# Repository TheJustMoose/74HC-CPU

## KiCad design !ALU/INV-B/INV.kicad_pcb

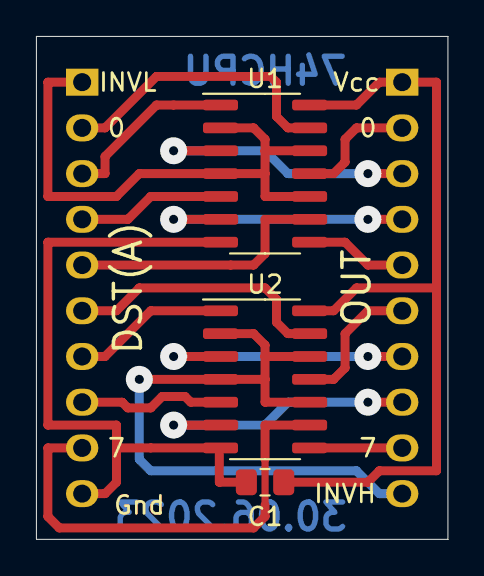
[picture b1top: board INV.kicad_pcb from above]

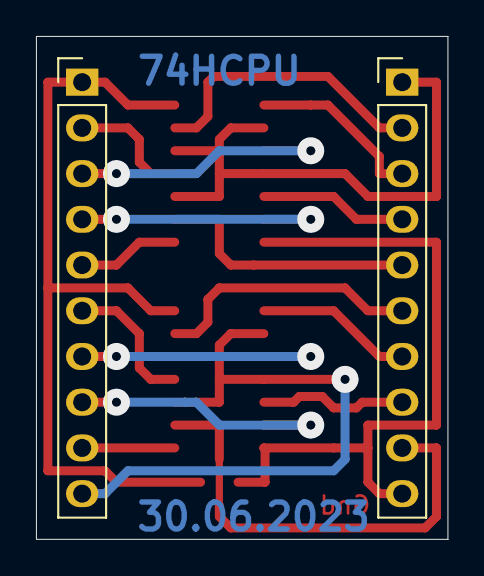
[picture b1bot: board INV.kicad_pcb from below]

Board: 2 copper layers, 22.9 x 27.9 mm, 5 parts (2 on the bottom side), 20 nets.

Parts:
C1: 0.1uF; C_0805_2012Metric_Pad1.18x1.45mm_HandSolder
J1, J2: Conn_01x10_Male; PinHeader_1x10_P2.54mm_Vertical
U1, U2: 74HC86; SO-14_3.9x8.65mm_P1.27mm

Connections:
/D0: J1.2, U1.13
/D1: J1.3, U1.1
/D2: J1.4, U1.5
/D3: J1.5, U1.9
/D4: J1.6, U2.13
/D5: J1.7, U2.1
/D6: J1.8, U2.5
/D7: J1.9, U2.9
/INVH: J2.10, U2.2, U2.4, U2.10, U2.12
/INVL: J1.1, U1.2, U1.4, U1.10, U1.12
/O0: J2.2, U1.11
/O1: J2.3, U1.3
/O2: J2.4, U1.6
/O3: J2.5, U1.8
/O4: J2.6, U2.11
/O5: J2.7, U2.3
/O6: J2.8, U2.6
/O7: J2.9, U2.8
GND: C1.2, J1.10, U1.7, U2.7
VCC: C1.1, J2.1, U1.14, U2.14

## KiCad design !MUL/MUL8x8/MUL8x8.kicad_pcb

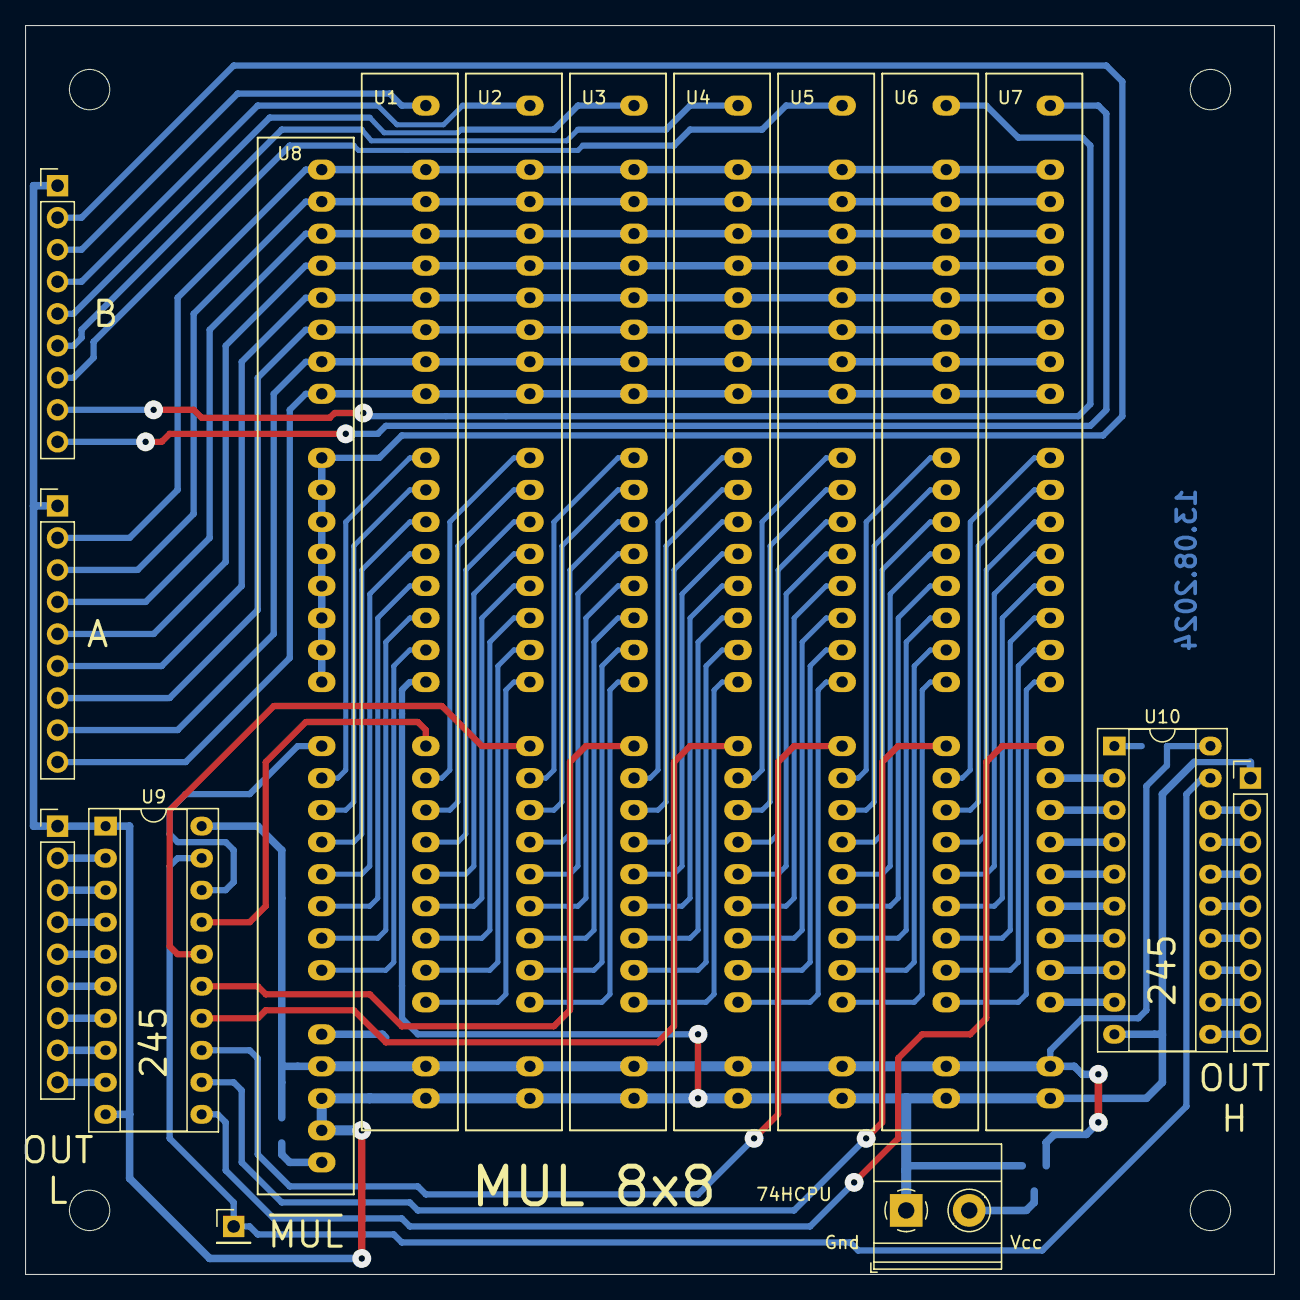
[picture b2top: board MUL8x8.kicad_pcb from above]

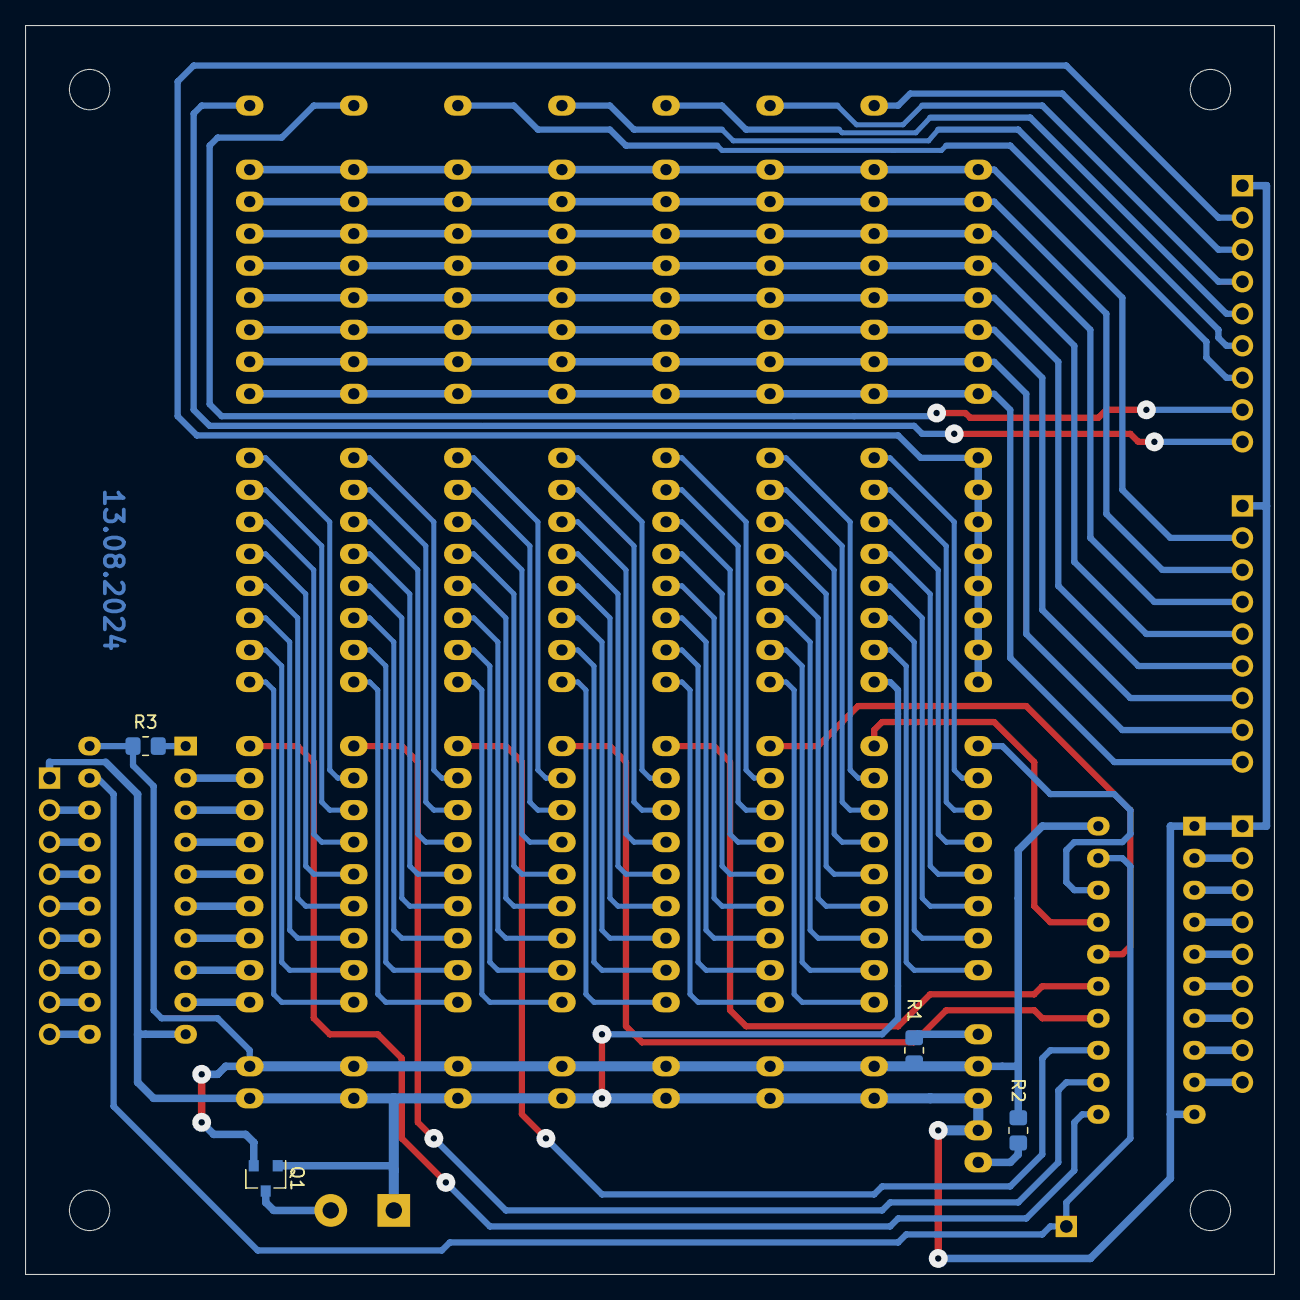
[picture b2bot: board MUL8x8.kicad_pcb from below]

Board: 2 copper layers, 99.1 x 99.1 mm, 24 parts (4 on the bottom side), 110 nets.

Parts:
H1, H2, H3, H4: MountingHole; MountingHole_3.2mm_M3
J1, J2, J3, J4: Conn_01x09_Male; PinHeader_1x09_P2.54mm_Vertical
J5: Conn_01x01_Male; PinHeader_1x01_P2.54mm_Vertical
J6: Screw_Terminal_01x02; TerminalBlock_Phoenix_MKDS-1,5-2_1x02_P5.00mm_Horizontal
Q1: IRLML5203; SOT-23
R1, R2, R3: 10k; R_0805_2012Metric_Pad1.20x1.40mm_HandSolder
U1, U2, U3, U4, U5, U6, U7: MUL1
U8: CMD
U9, U10: 74HC245; DIP-20_W7.62mm_Socket

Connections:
/A0: J1.2, U1.2, U2.2, U3.2, U4.2, U5.2, U6.2, U7.2, U8.1
/A1: J1.3, U1.3, U2.3, U3.3, U4.3, U5.3, U6.3, U7.3, U8.2
/A2: J1.4, U1.4, U2.4, U3.4, U4.4, U5.4, U6.4, U7.4, U8.3
/A3: J1.5, U1.5, U2.5, U3.5, U4.5, U5.5, U6.5, U7.5, U8.4
/A4: J1.6, U1.6, U2.6, U3.6, U4.6, U5.6, U6.6, U7.6, U8.5
/A5: J1.7, U1.7, U2.7, U3.7, U4.7, U5.7, U6.7, U7.7, U8.6
/A6: J1.8, U1.8, U2.8, U3.8, U4.8, U5.8, U6.8, U7.8, U8.7
/A7: J1.9, U1.9, U2.9, U3.9, U4.9, U5.9, U6.9, U7.9, U8.8
/B0: J2.2, U8.9, U8.10, U8.11, U8.12, U8.13, U8.14, U8.15, U8.16
/B1: J2.3, U1.1
/B2: J2.4, U2.1
/B3: J2.5, U3.1
/B4: J2.6, U4.1
/B5: J2.7, U5.1
/B6: J2.8, U6.1
/B7: J2.9, U7.1
/M0: J3.2, U9.2
/M1: J3.3, U9.3
/M2: J3.4, U9.4
/M3: J3.5, U9.5
/M4: J3.6, U9.6
/M5: J3.7, U9.7
/M6: J3.8, U9.8
/M7: J3.9, U9.9
/M8: J4.2, U10.18
/M9: J4.3, U10.17
/M10: J4.4, U10.16
/M11: J4.5, U10.15
/M12: J4.6, U10.14
/M13: J4.7, U10.13
/M14: J4.8, U10.12
/M15: J4.9, U10.11
/P0: U8.17, U9.18
/P1: U1.18, U9.17
/P2: U2.18, U9.16
/P3: U3.18, U9.15
/P4: U4.18, U9.14
/P5: U5.18, U9.13
/P6: U6.18, U9.12
/P7: U7.18, U9.11
/P8: U7.19, U10.2
/P9: U7.20, U10.3
/P10: U7.21, U10.4
/P11: U7.22, U10.5
/P12: U7.23, U10.6
/P13: U7.24, U10.7
/P14: U7.25, U10.8
/P15: U7.26, U10.9
/~MUL: J5.1, U9.19, U10.19
GND: J1.1, J2.1, J3.1, J4.1, J6.1, Q1.1, U1.17, U1.28, U2.28, U3.28, U4.28, U5.28, U6.28, U7.28, U8.27, U8.28, U9.1, U9.10, U10.10
unnamed: J6.2, Q1.3
unnamed: R1.2, U8.25
unnamed: R2.1, U8.29
unnamed: R3.1, U10.1
unnamed: U1.10, U8.18
unnamed: U1.11, U8.19
unnamed: U1.12, U8.20
unnamed: U1.13, U8.21
unnamed: U1.14, U8.22
unnamed: U1.15, U8.23
unnamed: U1.16, U8.24
unnamed: U1.19, U2.10
unnamed: U1.20, U2.11
unnamed: U1.21, U2.12
unnamed: U1.22, U2.13
unnamed: U1.23, U2.14
unnamed: U1.24, U2.15
unnamed: U1.25, U2.16
unnamed: U1.26, U2.17
unnamed: U2.19, U3.10
unnamed: U2.20, U3.11
unnamed: U2.21, U3.12
unnamed: U2.22, U3.13
unnamed: U2.23, U3.14
unnamed: U2.24, U3.15
unnamed: U2.25, U3.16
unnamed: U2.26, U3.17
unnamed: U3.19, U4.10
unnamed: U3.20, U4.11
unnamed: U3.21, U4.12
unnamed: U3.22, U4.13
unnamed: U3.23, U4.14
unnamed: U3.24, U4.15
unnamed: U3.25, U4.16
unnamed: U3.26, U4.17
unnamed: U4.19, U5.10
unnamed: U4.20, U5.11
unnamed: U4.21, U5.12
unnamed: U4.22, U5.13
unnamed: U4.23, U5.14
unnamed: U4.24, U5.15
unnamed: U4.25, U5.16
unnamed: U4.26, U5.17
unnamed: U5.19, U6.10
unnamed: U5.20, U6.11
unnamed: U5.21, U6.12
unnamed: U5.22, U6.13
unnamed: U5.23, U6.14
unnamed: U5.24, U6.15
unnamed: U5.25, U6.16
unnamed: U5.26, U6.17
unnamed: U6.19, U7.10
unnamed: U6.20, U7.11
unnamed: U6.21, U7.12
unnamed: U6.22, U7.13
unnamed: U6.23, U7.14
unnamed: U6.24, U7.15
unnamed: U6.25, U7.16
unnamed: U6.26, U7.17
VCC: Q1.2, R1.1, R2.2, R3.2, U1.27, U2.27, U3.27, U4.27, U5.27, U6.27, U7.27, U8.26, U9.20, U10.20

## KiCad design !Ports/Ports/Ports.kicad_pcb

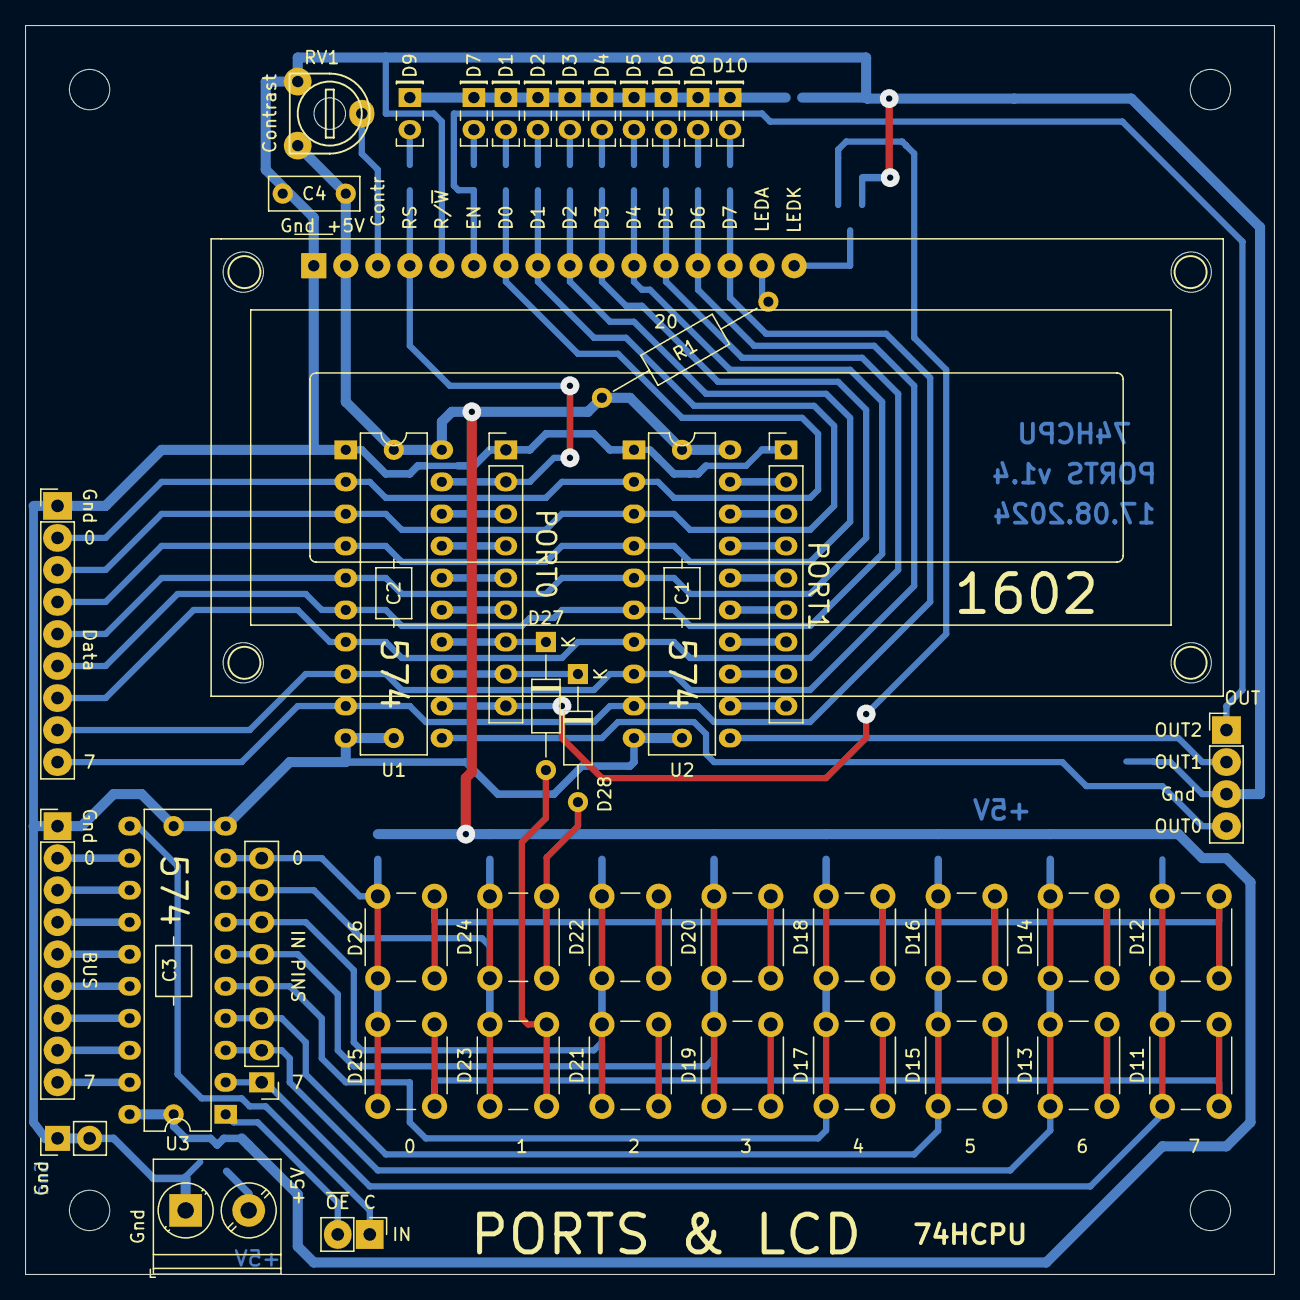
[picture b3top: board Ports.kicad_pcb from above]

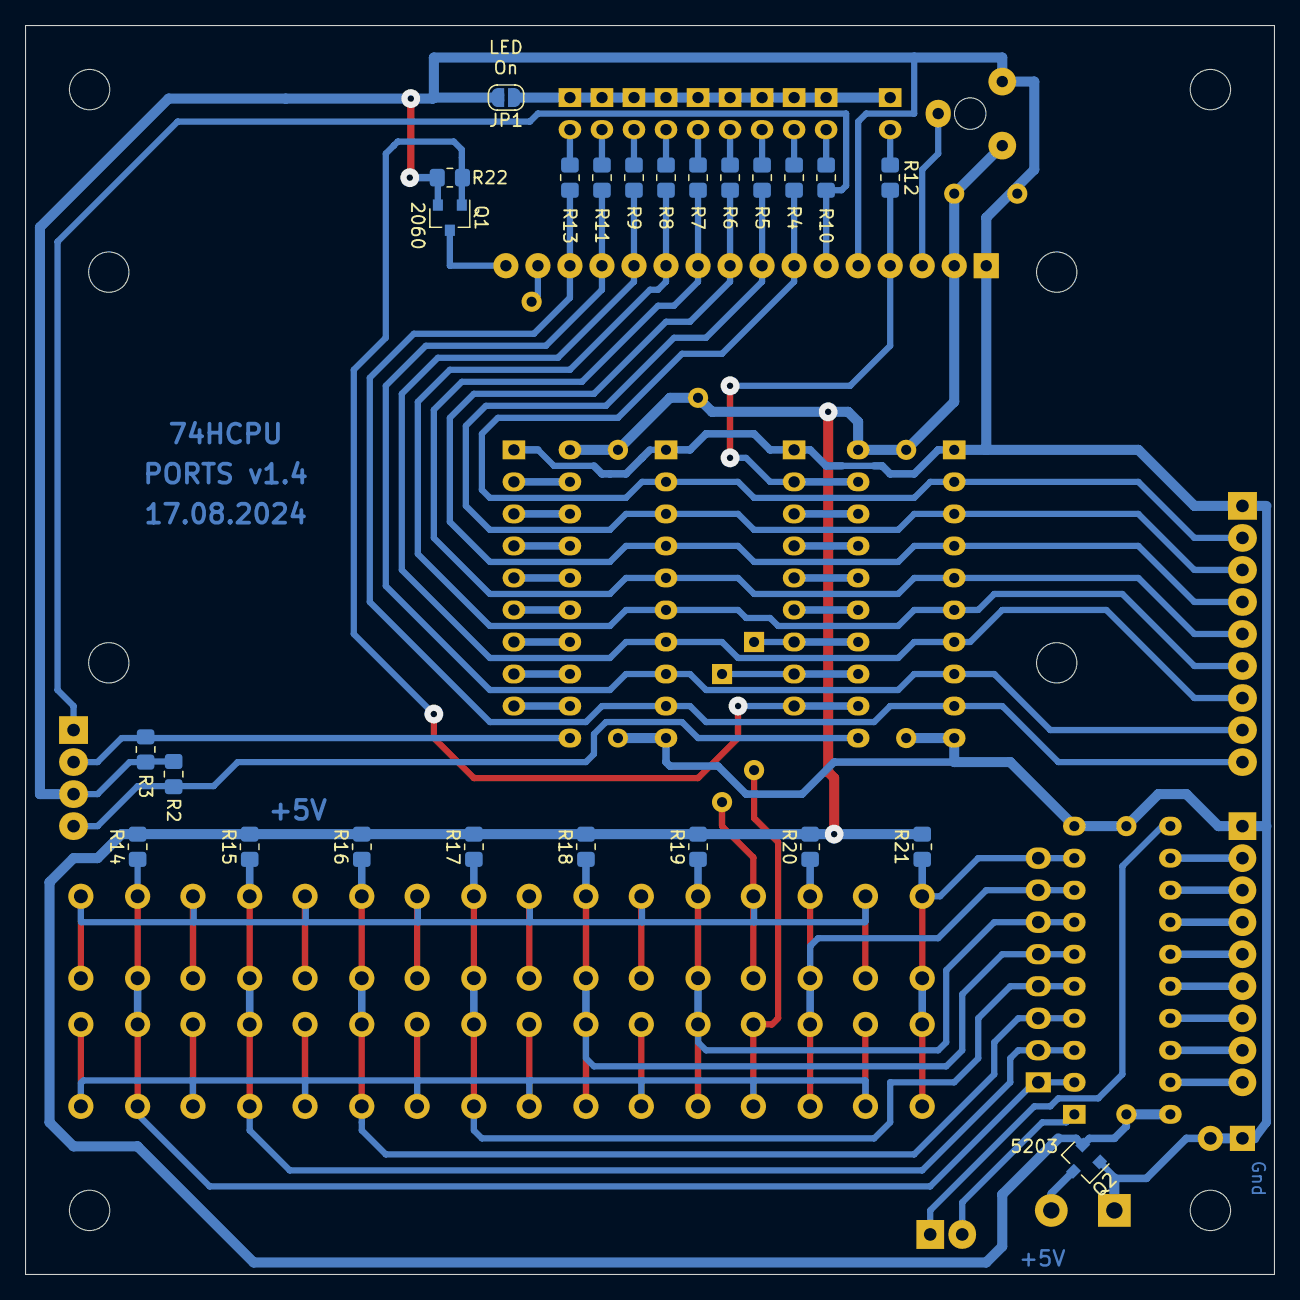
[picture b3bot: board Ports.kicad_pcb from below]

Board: 2 copper layers, 99.1 x 99.1 mm, 79 parts (24 on the bottom side), 64 nets.

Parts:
C1, C2, C3: 0.1uF; C_Axial_L3.8mm_D2.6mm_P22.86mm_Horizontal
C4: 0.1uF; C_Disc_D7.0mm_W2.5mm_P5.00mm
D1, D2, D3, D4, D5, D6, D7, D8, D9, D10: LED; LED_Rectangular_W5.0mm_H2.0mm
D11, D12, D13, D14, D15, D16, D17, D18, D19, D20, D21, D22, D23, D24, D25, D26: 6x6-tact-btn; SW_PUSH_6mm_H4.3mm
D27, D28: 1N4148; D_DO-35_SOD27_P10.16mm_Horizontal
DS1: WC1602A; WH1602-2-holes
H1, H2, H3, H4, H5, H6, H7, H8: MountingHole; MountingHole_3.2mm_M3
J1, J2, J3, J6: Conn_01x09_Male; PinHeader_1x09_P2.54mm_Vertical
J4: Screw_Terminal_01x02; TerminalBlock_Phoenix_PT-1,5-2-5.0-H_1x02_P5.00mm_Horizontal
J5: Conn_01x04_Male; PinHeader_1x04_P2.54mm_Vertical
J7, J9: Conn_01x02_Male; PinHeader_1x02_P2.54mm_Vertical
J8: Conn_01x08_Male; PinHeader_1x08_P2.54mm_Vertical
JP1: Jumper; SolderJumper-2_P1.3mm_Open_RoundedPad1.0x1.5mm
Q1: IRLML2060; SOT-23
Q2: IRLML5203; SOT-23
R1: 20; R_Axial_DIN0207_L6.3mm_D2.5mm_P15.24mm_Horizontal
R2, R3, R14, R15, R16, R17, R18, R19, R20, R21, R22: 10k; R_0805_2012Metric_Pad1.20x1.40mm_HandSolder
R4, R5, R6, R7, R8, R9, R10, R11, R12, R13: 1k; R_0805_2012Metric_Pad1.20x1.40mm_HandSolder
RV1: R_POT; pot-5x5
U1, U2, U3: 74LS574; DIP-20_W7.62mm

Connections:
/BUS0: J6.2, U3.12
/BUS1: J6.3, U3.13
/BUS2: J6.4, U3.14
/BUS3: J6.5, U3.15
/BUS4: J6.6, U3.16
/BUS5: J6.7, U3.17
/BUS6: J6.8, U3.18
/BUS7: J6.9, U3.19
/D0: DS1.7, J1.2, R4.2, U1.2, U2.2
/D1: DS1.8, J1.3, R5.2, U1.3, U2.3
/D2: DS1.9, J1.4, R6.2, U1.4, U2.4
/D3: DS1.10, J1.5, R7.2, U1.5, U2.5
/D4: DS1.11, J1.6, R8.2, U1.6, U2.6
/D5: DS1.12, J1.7, R9.2, U1.7, U2.7
/D6: DS1.13, J1.8, R11.2, U1.8, U2.8
/D7: DS1.14, J1.9, R13.2, U1.9, U2.9
/IN0.0: D25.1, D26.1, J8.8, R21.1, U3.9
/IN0.1: D23.1, D24.1, J8.7, R20.1, U3.8
/IN0.2: D21.1, D22.1, J8.6, R19.1, U3.7
/IN0.3: D19.1, D20.1, J8.5, R18.1, U3.6
/IN0.4: D17.1, D18.1, J8.4, R17.1, U3.5
/IN0.5: D15.1, D16.1, J8.3, R16.1, U3.4
/IN0.6: D13.1, D14.1, J8.2, R15.1, U3.3
/IN0.7: D11.1, D12.1, J8.1, R14.1, U3.2
/IN0.C: J7.1, U3.11
/IN0.OE: J7.2, U3.1
/OUT0: J5.4, R2.1, U1.11
/OUT1: J5.2, R3.1, U2.11
/OUT2: DS1.6, J5.1, R10.2
/P0.0: DS1.4, J2.2, R12.2, U1.19
/P0.1: J2.3, U1.18
/P0.2: J2.4, U1.17
/P0.3: J2.5, U1.16
/P0.4: J2.6, U1.15
/P0.5: D27.1, J2.7, U1.14
/P0.6: D28.1, J2.8, U1.13
/P0.7: J2.9, Q1.1, R22.1, U1.12
/P1.0: J3.2, U2.19
/P1.1: J3.3, U2.18
/P1.2: J3.4, U2.17
/P1.3: J3.5, U2.16
/P1.4: J3.6, U2.15
/P1.5: J3.7, U2.14
/P1.6: J3.8, U2.13
/P1.7: J3.9, U2.12
GND: C1.2, C2.2, C3.2, C4.2, DS1.1, DS1.5, J1.1, J2.1, J3.1, J4.1, J5.3, J6.1, J9.1, J9.2, JP1.2, Q1.2, Q2.1, R2.2, R3.2, R22.2, RV1.1, U1.1, U1.10, U2.1, U2.10, U3.10
unnamed: D1.1, D2.1, D3.1, D4.1, D5.1, D6.1, D7.1, D8.1, D9.1, D10.1, JP1.1
unnamed: D1.2, R4.1
unnamed: D2.2, R5.1
unnamed: D3.2, R6.1
unnamed: D4.2, R7.1
unnamed: D5.2, R8.1
unnamed: D6.2, R9.1
unnamed: D7.2, R10.1
unnamed: D8.2, R11.1
unnamed: D9.2, R12.1
unnamed: D10.2, R13.1
unnamed: D11.2, D13.2, D15.2, D17.2, D19.2, D21.2, D23.2, D25.2, D27.2
unnamed: D12.2, D14.2, D16.2, D18.2, D20.2, D22.2, D24.2, D26.2, D28.2
unnamed: DS1.3, RV1.2
unnamed: DS1.15, R1.2
unnamed: DS1.16, Q1.3
unnamed: J4.2, Q2.3
VCC: C1.1, C2.1, C3.1, C4.1, DS1.2, Q2.2, R1.1, R14.2, R15.2, R16.2, R17.2, R18.2, R19.2, R20.2, R21.2, RV1.3, U1.20, U2.20, U3.20

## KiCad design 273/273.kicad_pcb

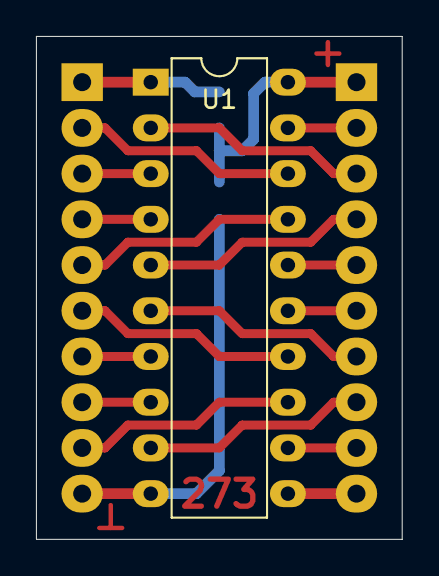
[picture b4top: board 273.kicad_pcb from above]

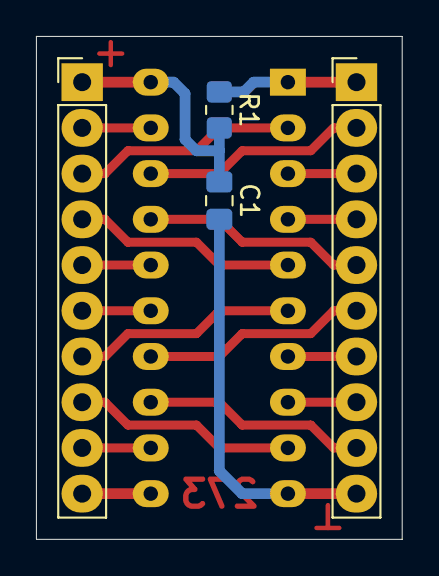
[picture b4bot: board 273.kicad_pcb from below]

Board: 2 copper layers, 20.3 x 27.9 mm, 5 parts (4 on the bottom side), 20 nets.

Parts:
C1: 0.1uF; C_0805_2012Metric_Pad1.18x1.45mm_HandSolder
J1, J2: Conn_01x10_Male; PinHeader_1x10_P2.54mm_Vertical
R1: 10k; R_0805_2012Metric_Pad1.20x1.40mm_HandSolder
U1: 74HC273; DIP-20_W7.62mm

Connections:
/CP: J2.10, U1.11
/D0: J1.2, U1.18
/D1: J1.3, U1.3
/D2: J1.4, U1.4
/D3: J1.5, U1.17
/D4: J1.6, U1.14
/D5: J1.7, U1.7
/D6: J1.8, U1.8
/D7: J1.9, U1.13
/GND: C1.2, J1.10, U1.10
/Q0: J2.2, U1.19
/Q1: J2.3, U1.2
/Q2: J2.4, U1.5
/Q3: J2.5, U1.16
/Q4: J2.6, U1.15
/Q5: J2.7, U1.6
/Q6: J2.8, U1.9
/Q7: J2.9, U1.12
/VCC: C1.1, J2.1, R1.2, U1.20
/~MR: J1.1, R1.1, U1.1

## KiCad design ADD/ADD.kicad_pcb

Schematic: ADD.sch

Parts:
C1: 0.1uF; C_0805_2012Metric_Pad1.18x1.45mm_HandSolder
D1: LED; LED_0805_2012Metric_Pad1.15x1.40mm_HandSolder
J1, J2, J3: Conn_01x08_Male; PinHeader_1x08_P2.54mm_Horizontal
J4: Conn_01x05_Male; PinHeader_1x05_P2.54mm_Horizontal
J5, J6: Conn_01x01_Male; PinHeader_1x01_P2.54mm_Vertical
R1: 1k; R_0805_2012Metric_Pad1.20x1.40mm_HandSolder
R2, R3: 10k; R_0805_2012Metric_Pad1.20x1.40mm_HandSolder
U1, U2: 74LS283; DIP-16_W7.62mm
U3: 74LS573; DIP-20_W7.62mm
U4: 74HC00; DIP-14_W7.62mm

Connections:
/A0: J2.8, U1.5 (A1)
/A1: J2.7, U1.3 (A2)
/A2: J2.6, U1.14 (A3)
/A3: J2.5, U1.12 (A4)
/A4: J2.4, U2.5 (A1)
/A5: J2.3, U2.3 (A2)
/A6: J2.2, U2.14 (A3)
/A7: J2.1, U2.12 (A4)
/ADD_CIN: J5.1, U4.2
/B0: J1.8, U1.6 (B1)
/B1: J1.7, U1.2 (B2)
/B2: J1.6, U1.15 (B3)
/B3: J1.5, U1.11 (B4)
/B4: J1.4, U2.6 (B1)
/B5: J1.3, U2.2 (B2)
/B6: J1.2, U2.15 (B3)
/B7: J1.1, U2.11 (B4)
/Latch: J4.5, R2.1, U3.11 (Load)
/O0: J3.8, U3.12 (Q7)
/O1: J3.7, U3.13 (Q6)
/O2: J3.6, U3.14 (Q5)
/O3: J3.5, U3.15 (Q4)
/O4: J3.4, U3.16 (Q3)
/O5: J3.3, U3.17 (Q2)
/O6: J3.2, U3.18 (Q1)
/O7: J3.1, U3.19 (Q0)
/UseCF: J4.2, R3.1, U4.1
/auxiliary_carry: U1.9 (C4), U2.7 (C0); also elsewhere on the board
/~(ADD_COUT&OE): J6.1, U4.8
/~OE: J4.1, R1.2, U3.1 (OE), U4.12, U4.13
GND: C1.2, J4.3, R2.2, R3.2, U1.8 (GND), U2.8 (GND), U3.10 (GND), U4.7
unnamed: D1.1 (K), R1.1
unnamed: U1.1 (S2), U3.8 (D6)
unnamed: U1.4 (S1), U3.9 (D7)
unnamed: U1.7 (C0), U4.6
unnamed: U1.10 (S4), U3.6 (D4)
unnamed: U1.13 (S3), U3.7 (D5)
unnamed: U2.1 (S2), U3.4 (D2)
unnamed: U2.4 (S1), U3.5 (D3)
unnamed: U2.9 (C4), U4.9
unnamed: U2.10 (S4), U3.2 (D0)
unnamed: U2.13 (S3), U3.3 (D1)
unnamed: U4.3, U4.4, U4.5
unnamed: U4.10, U4.11
VCC: C1.1, D1.2 (A), J4.4, U1.16 (VCC), U2.16 (VCC), U3.20 (VCC), U4.14

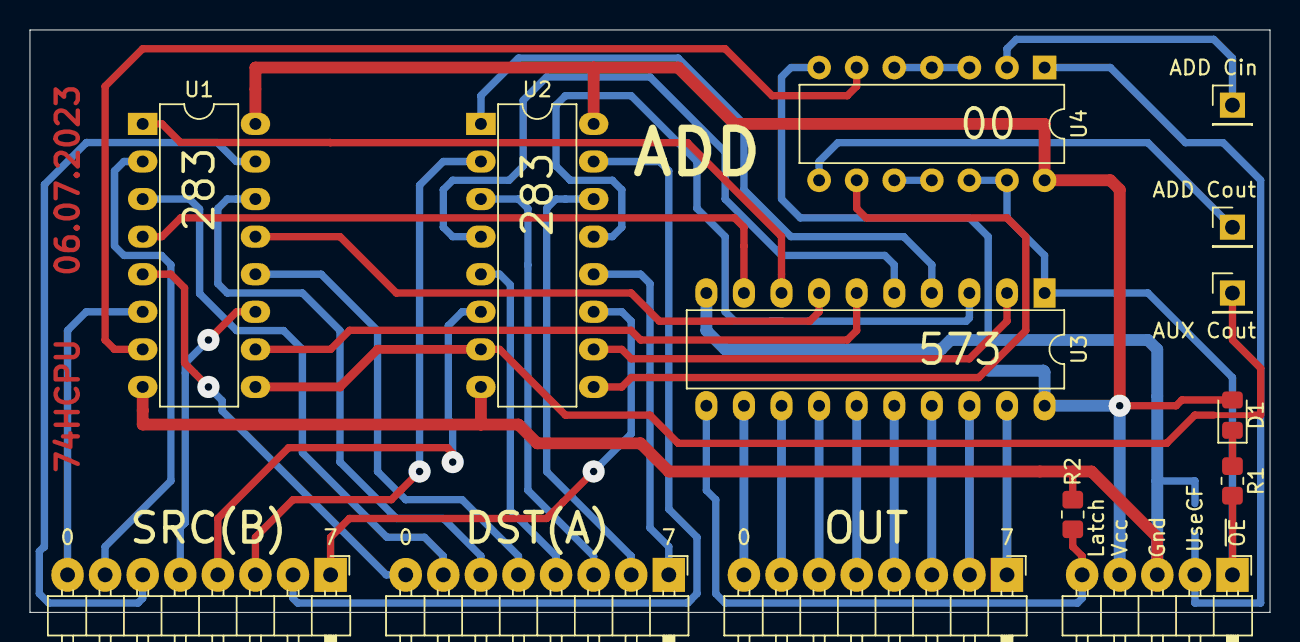
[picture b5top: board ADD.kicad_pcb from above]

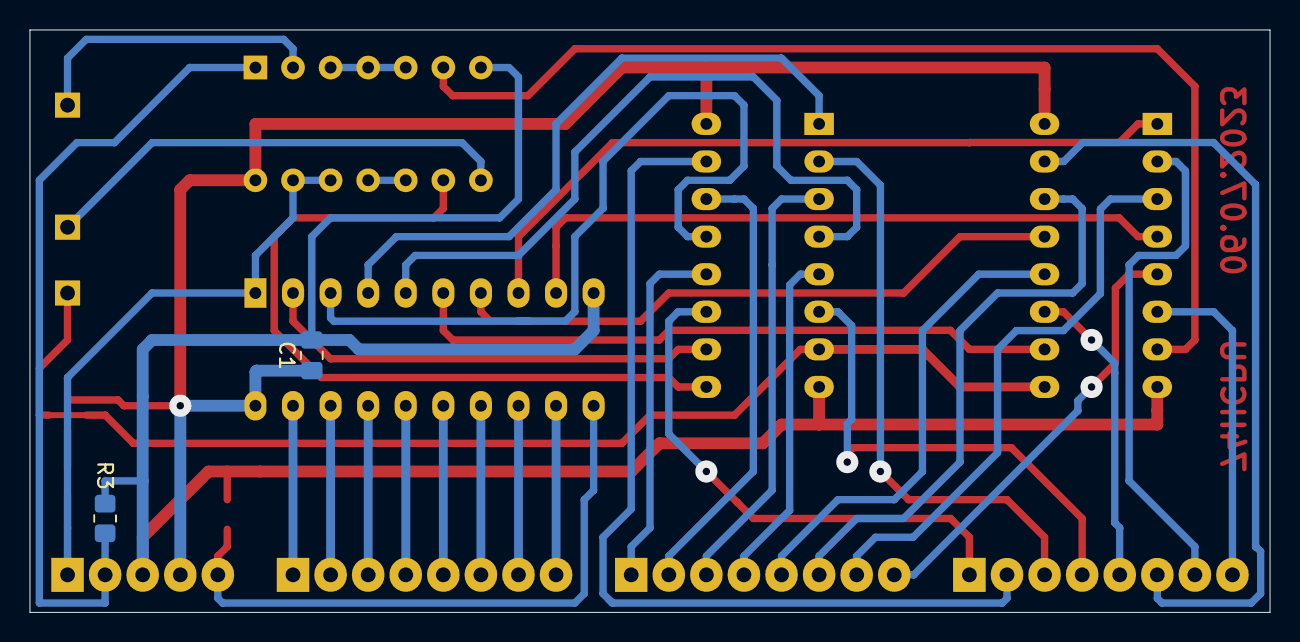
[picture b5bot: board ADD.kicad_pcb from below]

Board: 2 copper layers, 83.8 x 39.4 mm, 16 parts (2 on the bottom side), 45 nets.

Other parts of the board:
J7: Conn_01x01_Male; PinHeader_1x01_P2.54mm_Vertical

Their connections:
/auxiliary_carry: J7.1; also elsewhere on the board

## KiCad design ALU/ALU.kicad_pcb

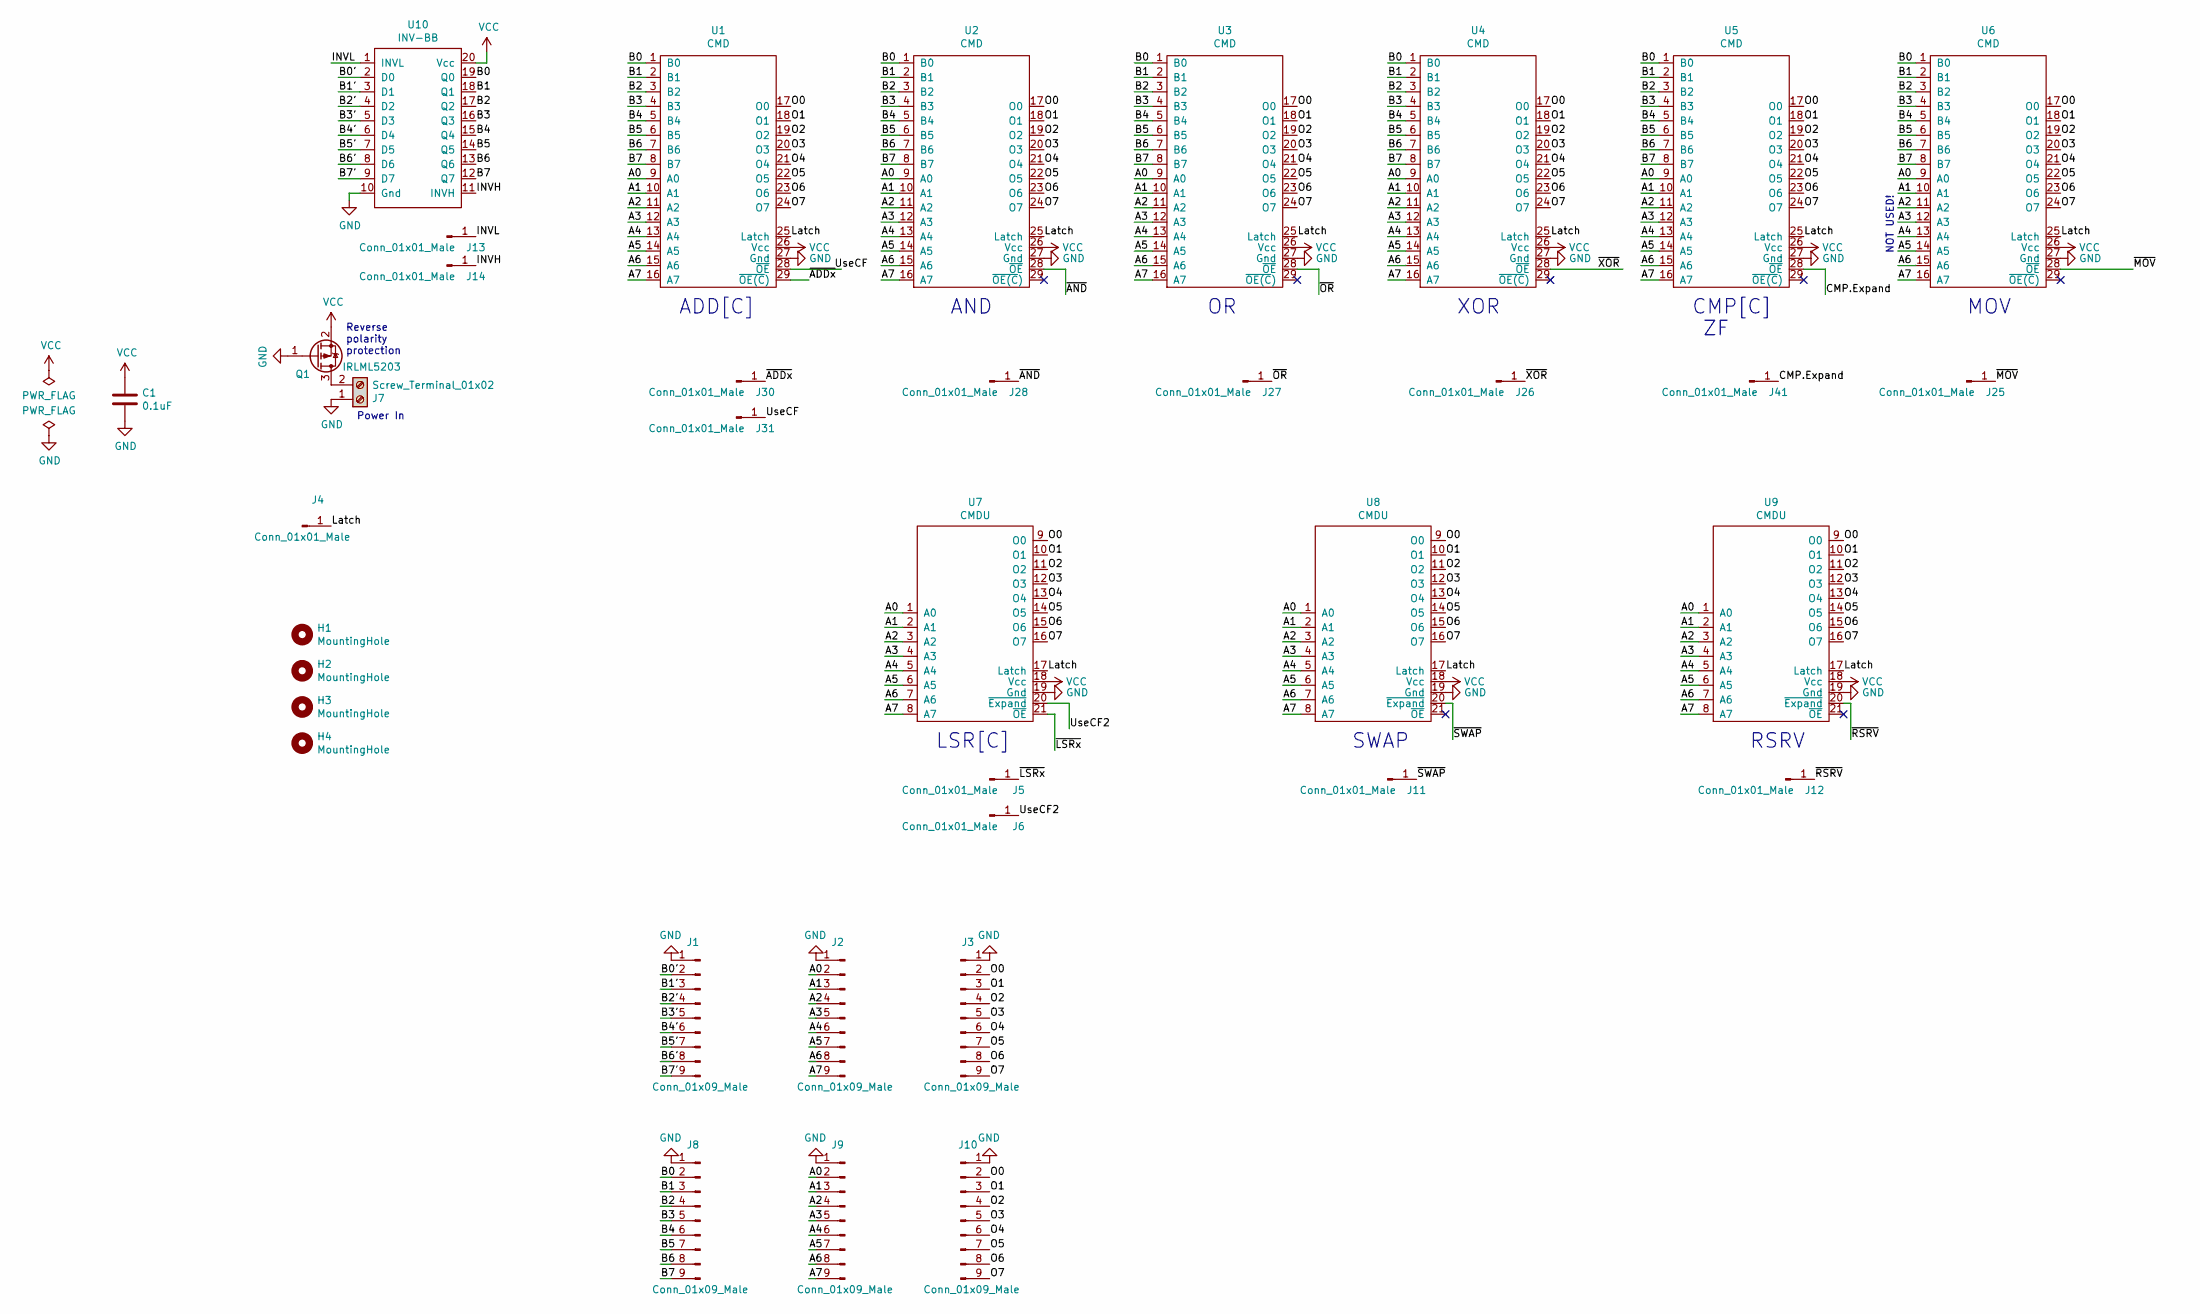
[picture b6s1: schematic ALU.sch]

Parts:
C1: 0.1uF; C_0805_2012Metric_Pad1.18x1.45mm_HandSolder
H1, H2, H3, H4: MountingHole; MountingHole_3.2mm_M3
J1, J2, J3, J8, J9, J10: Conn_01x09_Male; PinHeader_1x09_P2.54mm_Vertical
J4, J5, J6, J11, J12, J13, J14, J25, J26, J27, J28, J30, J31, J41: Conn_01x01_Male; PinHeader_1x01_P2.54mm_Vertical
J7: Screw_Terminal_01x02; TerminalBlock_Phoenix_MKDS-1,5-2_1x02_P5.00mm_Horizontal
Q1: IRLML5203; SOT-23
U1, U2, U3, U4, U5, U6: CMD
U7, U8, U9: CMDU
U10: INV-BB; INV-B

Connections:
/A0: J2.2, J9.2, U1.9 (A0), U2.9 (A0), U3.9 (A0), U4.9 (A0), U5.9 (A0), U6.9 (A0), U7.1 (A0), U8.1 (A0), U9.1 (A0)
/A1: J2.3, J9.3, U1.10 (A1), U2.10 (A1), U3.10 (A1), U4.10 (A1), U5.10 (A1), U6.10 (A1), U7.2 (A1), U8.2 (A1), U9.2 (A1)
/A2: J2.4, J9.4, U1.11 (A2), U2.11 (A2), U3.11 (A2), U4.11 (A2), U5.11 (A2), U6.11 (A2), U7.3 (A2), U8.3 (A2), U9.3 (A2)
/A3: J2.5, J9.5, U1.12 (A3), U2.12 (A3), U3.12 (A3), U4.12 (A3), U5.12 (A3), U6.12 (A3), U7.4 (A3), U8.4 (A3), U9.4 (A3)
/A4: J2.6, J9.6, U1.13 (A4), U2.13 (A4), U3.13 (A4), U4.13 (A4), U5.13 (A4), U6.13 (A4), U7.5 (A4), U8.5 (A4), U9.5 (A4)
/A5: J2.7, J9.7, U1.14 (A5), U2.14 (A5), U3.14 (A5), U4.14 (A5), U5.14 (A5), U6.14 (A5), U7.6 (A5), U8.6 (A5), U9.6 (A5)
/A6: J2.8, J9.8, U1.15 (A6), U2.15 (A6), U3.15 (A6), U4.15 (A6), U5.15 (A6), U6.15 (A6), U7.7 (A6), U8.7 (A6), U9.7 (A6)
/A7: J2.9, J9.9, U1.16 (A7), U2.16 (A7), U3.16 (A7), U4.16 (A7), U5.16 (A7), U6.16 (A7), U7.8 (A7), U8.8 (A7), U9.8 (A7)
/B0: J8.2, U1.1 (B0), U2.1 (B0), U3.1 (B0), U4.1 (B0), U5.1 (B0), U6.1 (B0), U10.19 (Q0)
/B0': J1.2, U10.2 (D0)
/B1: J8.3, U1.2 (B1), U2.2 (B1), U3.2 (B1), U4.2 (B1), U5.2 (B1), U6.2 (B1), U10.18 (Q1)
/B1': J1.3, U10.3 (D1)
/B2: J8.4, U1.3 (B2), U2.3 (B2), U3.3 (B2), U4.3 (B2), U5.3 (B2), U6.3 (B2), U10.17 (Q2)
/B2': J1.4, U10.4 (D2)
/B3: J8.5, U1.4 (B3), U2.4 (B3), U3.4 (B3), U4.4 (B3), U5.4 (B3), U6.4 (B3), U10.16 (Q3)
/B3': J1.5, U10.5 (D3)
/B4: J8.6, U1.5 (B4), U2.5 (B4), U3.5 (B4), U4.5 (B4), U5.5 (B4), U6.5 (B4), U10.15 (Q4)
/B4': J1.6, U10.6 (D4)
/B5: J8.7, U1.6 (B5), U2.6 (B5), U3.6 (B5), U4.6 (B5), U5.6 (B5), U6.6 (B5), U10.14 (Q5)
/B5': J1.7, U10.7 (D5)
/B6: J8.8, U1.7 (B6), U2.7 (B6), U3.7 (B6), U4.7 (B6), U5.7 (B6), U6.7 (B6), U10.13 (Q6)
/B6': J1.8, U10.8 (D6)
/B7: J8.9, U1.8 (B7), U2.8 (B7), U3.8 (B7), U4.8 (B7), U5.8 (B7), U6.8 (B7), U10.12 (Q7)
/B7': J1.9, U10.9 (D7)
/CMP.Expand: J41.1, U5.28 (~OE)
/INVH: J14.1, U10.11 (INVH); also elsewhere on the board
/INVL: J13.1, U10.1 (INVL); also elsewhere on the board
/Latch: J4.1, U1.25 (Latch), U2.25 (Latch), U3.25 (Latch), U4.25 (Latch), U5.25 (Latch), U6.25 (Latch), U7.17 (Latch), U8.17 (Latch), U9.17 (Latch); also elsewhere on the board
/O0: J3.2, J10.2, U1.17 (O0), U2.17 (O0), U3.17 (O0), U4.17 (O0), U5.17 (O0), U6.17 (O0), U7.9 (O0), U8.9 (O0), U9.9 (O0)
/O1: J3.3, J10.3, U1.18 (O1), U2.18 (O1), U3.18 (O1), U4.18 (O1), U5.18 (O1), U6.18 (O1), U7.10 (O1), U8.10 (O1), U9.10 (O1)
/O2: J3.4, J10.4, U1.19 (O2), U2.19 (O2), U3.19 (O2), U4.19 (O2), U5.19 (O2), U6.19 (O2), U7.11 (O2), U8.11 (O2), U9.11 (O2)
/O3: J3.5, J10.5, U1.20 (O3), U2.20 (O3), U3.20 (O3), U4.20 (O3), U5.20 (O3), U6.20 (O3), U7.12 (O3), U8.12 (O3), U9.12 (O3)
/O4: J3.6, J10.6, U1.21 (O4), U2.21 (O4), U3.21 (O4), U4.21 (O4), U5.21 (O4), U6.21 (O4), U7.13 (O4), U8.13 (O4), U9.13 (O4)
/O5: J3.7, J10.7, U1.22 (O5), U2.22 (O5), U3.22 (O5), U4.22 (O5), U5.22 (O5), U6.22 (O5), U7.14 (O5), U8.14 (O5), U9.14 (O5)
/O6: J3.8, J10.8, U1.23 (O6), U2.23 (O6), U3.23 (O6), U4.23 (O6), U5.23 (O6), U6.23 (O6), U7.15 (O6), U8.15 (O6), U9.15 (O6)
/O7: J3.9, J10.9, U1.24 (O7), U2.24 (O7), U3.24 (O7), U4.24 (O7), U5.24 (O7), U6.24 (O7), U7.16 (O7), U8.16 (O7), U9.16 (O7)
/UseCF: J31.1, U1.28 (~OE)
/UseCF2: J6.1, U7.20 (~Expand)
/~ADDx: J30.1, U1.29 (~OE(C))
/~AND: J28.1, U2.28 (~OE)
/~LSRx: J5.1, U7.21 (~OE)
/~MOV: J25.1, U6.28 (~OE)
/~OR: J27.1, U3.28 (~OE)
/~RSRV: J12.1, U9.20 (~Expand)
/~SWAP: J11.1, U8.20 (~Expand)
/~XOR: J26.1, U4.28 (~OE)
GND: C1.2, J1.1, J2.1, J3.1, J7.1, J8.1, J9.1, J10.1, Q1.1 (G), U1.27 (Gnd), U2.27 (Gnd), U3.27 (Gnd), U4.27 (Gnd), U5.27 (Gnd), U6.27 (Gnd), U7.19 (Gnd), U8.19 (Gnd), U9.19 (Gnd), U10.10 (Gnd); also elsewhere on the board
unnamed: J7.2, Q1.3 (D)
VCC: C1.1, Q1.2 (S), U1.26 (Vcc), U2.26 (Vcc), U3.26 (Vcc), U4.26 (Vcc), U5.26 (Vcc), U6.26 (Vcc), U7.18 (Vcc), U8.18 (Vcc), U9.18 (Vcc), U10.20 (Vcc); also elsewhere on the board

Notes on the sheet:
ADD[C]
AND
XOR
CMP[C]
LSR[C]
MOV
NOT USED!
SWAP
Power In
Reverse polarity protection
RSRV
